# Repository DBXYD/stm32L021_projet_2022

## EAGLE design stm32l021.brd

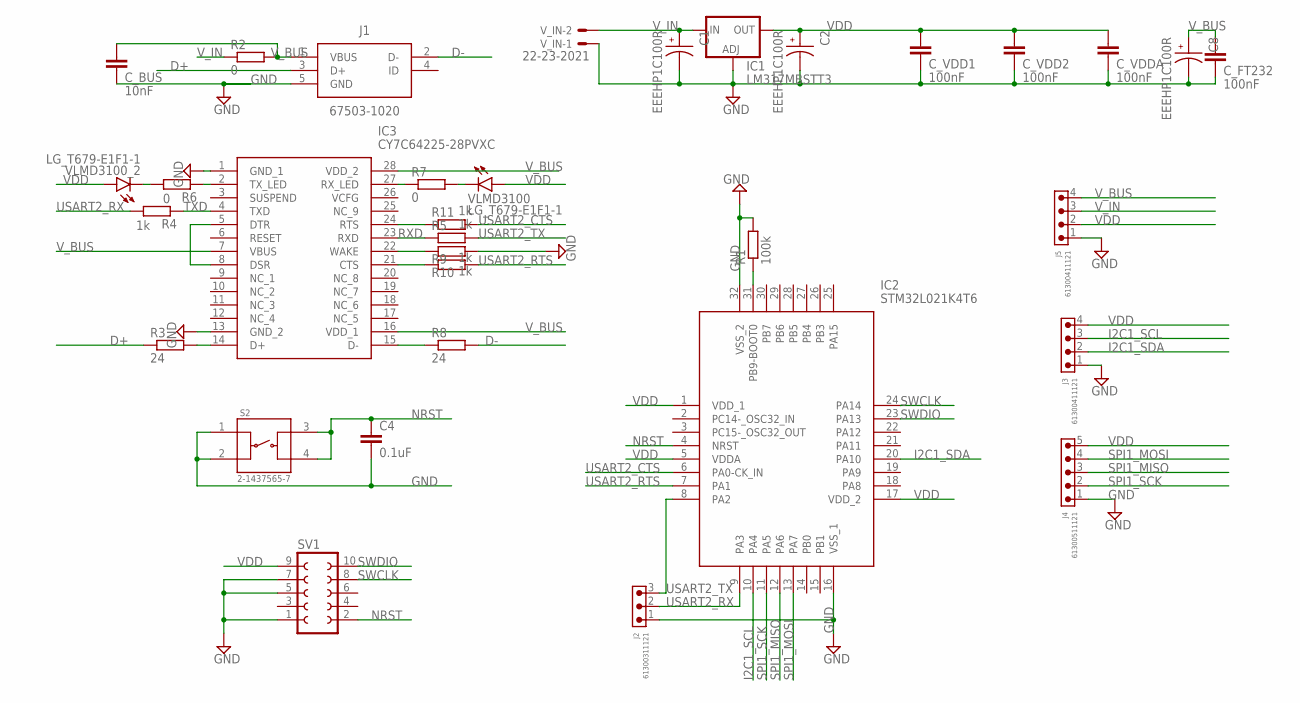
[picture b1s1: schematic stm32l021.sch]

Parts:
C1, C2, C8: EEEHP1C100R; CAP_EEEHP1C100R
C4: 0.1uF; C0603
C_BUS: 10nF; C0603
C_FT232: 100nF; C0603
C_VDD1, C_VDD2: 100nF; C0603
C_VDDA: 100nF; C0603
IC1: LM317MBSTT3; SOT223
IC2: STM32L021K4T6; QFP80P900X900X160-32N
IC3: CY7C64225-28PVXC; SOP65P780X185-28N
J1: 67503-1020
J2: 61300311121
J3, J5: 61300411121
J4: 61300511121
R1: 100k; R0603
R2, R6, R7: 0; R0603
R3, R8: 24; R0603
R4, R5, R9, R10, R11: 1k; R0603
S2: 2-1437565-7; SW_2-1437565-7
SV1: FE05-2
VLMD3100, VLMD3100_2: LG_T679-E1F1-1; PLCC2
V_IN: 22-23-2021

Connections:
D+: J1.3 (D+), R3.1
D-: J1.2 (D-), R8.2
GND: C1.2, C2.2, C4.2, C8.2, C_BUS.2, C_FT232.2, C_VDD1.2, C_VDD2.2, C_VDDA.2, IC1.1 (ADJ), IC2.16 (VSS_1), IC2.32 (VSS_2), IC3.1 (GND_1), IC3.13 (GND_2), J1.5 (GND), J2.1, J3.1, J4.1, J5.1, R1.2, R9.2, S2.1, S2.2, SV1.1, SV1.5, SV1.7, V_IN.1
I2C1_SCL: IC2.10 (PA4), J3.3
I2C1_SDA: IC2.20 (PA10), J3.2
unnamed: R6.2, VLMD3100_2.C
unnamed: IC2.31 (PB9-BOOT0), R1.1
unnamed: IC3.2 (TX_LED), R6.1
unnamed: IC3.27 (RX_LED), R7.1
unnamed: IC3.14 (D+), R3.2
unnamed: R7.2, VLMD3100.C
unnamed: IC3.5 (DTR), IC3.8 (DSR)
unnamed: IC3.15 (D-), R8.1
unnamed: IC3.22 (WAKE), R9.1
unnamed: IC3.24 (RTS), R11.1
unnamed: IC3.21 (CTS), R10.1
NRST: C4.1, IC2.4 (NRST), S2.3, S2.4, SV1.2
RXD: IC3.23 (RXD), R5.1
SPI1_MISO: IC2.12 (PA6), J4.3
SPI1_MOSI: IC2.13 (PA7), J4.4
SPI1_SCK: IC2.11 (PA5), J4.2
SWCLK: IC2.24 (PA14), SV1.8
SWDIO: IC2.23 (PA13), SV1.10
TXD: IC3.4 (TXD), R4.1
USART2_CTS: IC2.6 (PA0-CK_IN), R11.2
USART2_RTS: IC2.7 (PA1), R10.2
USART2_RX: IC2.9 (PA3), J2.2, R4.2
USART2_TX: IC2.8 (PA2), J2.3, R5.2
VDD: C2.1, C_VDD1.1, C_VDD2.1, C_VDDA.1, IC1.4 (OUT), IC2.1 (VDD_1), IC2.5 (VDDA), IC2.17 (VDD_2), J3.4, J4.5, J5.2, SV1.9, VLMD3100.A, VLMD3100_2.A
V_BUS: C8.1, C_BUS.1, C_FT232.1, IC3.7 (VBUS), IC3.16 (VDD_1), IC3.28 (VDD_2), J1.1 (VBUS), J5.4, R2.2
V_IN: C1.1, IC1.3 (IN), J5.3, R2.1, V_IN.2

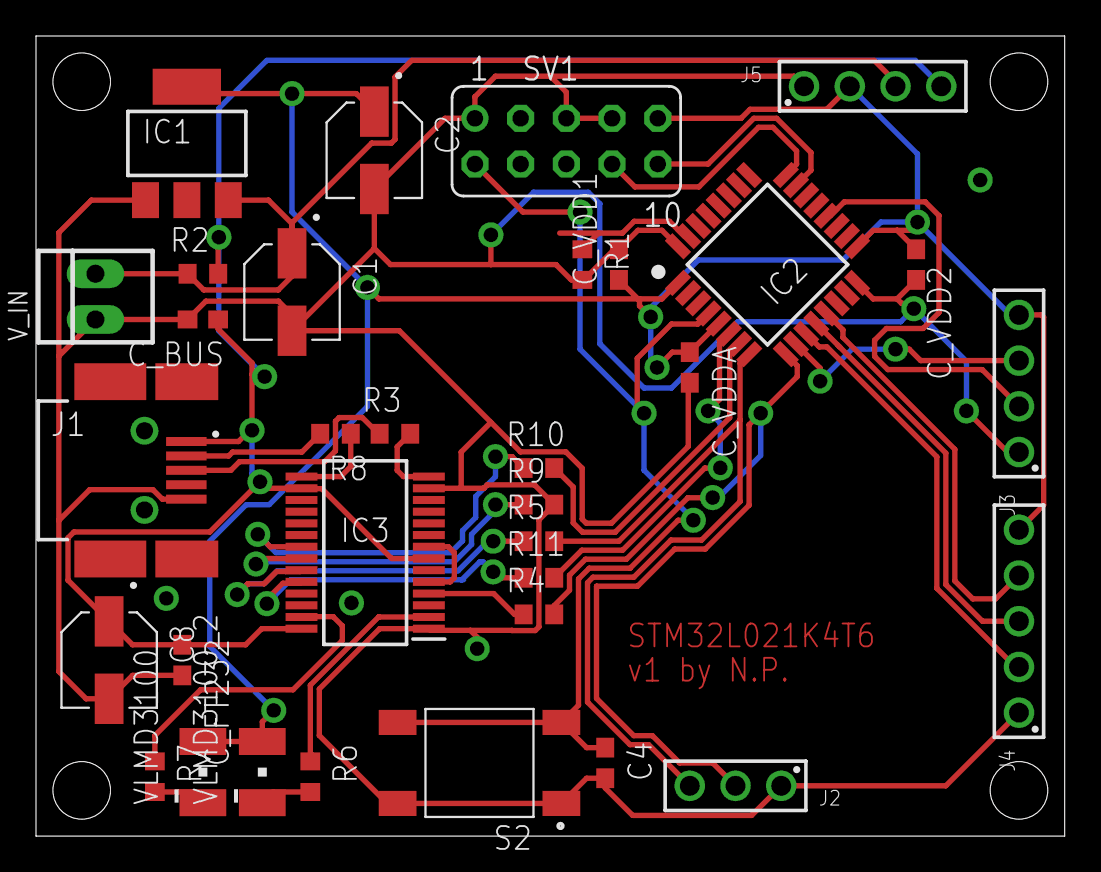
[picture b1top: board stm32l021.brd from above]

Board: 2 copper layers, 57.1 x 44.5 mm, 33 parts (0 on the bottom side), 31 nets.

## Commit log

2022-04-03 first version with stm32L021 uP
2022-04-03 add PCB view export
2022-04-11 14 pin smd connector

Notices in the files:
parts and their libraries:
Eagle_WR-PHD: Copyright: Würth Elektronik
